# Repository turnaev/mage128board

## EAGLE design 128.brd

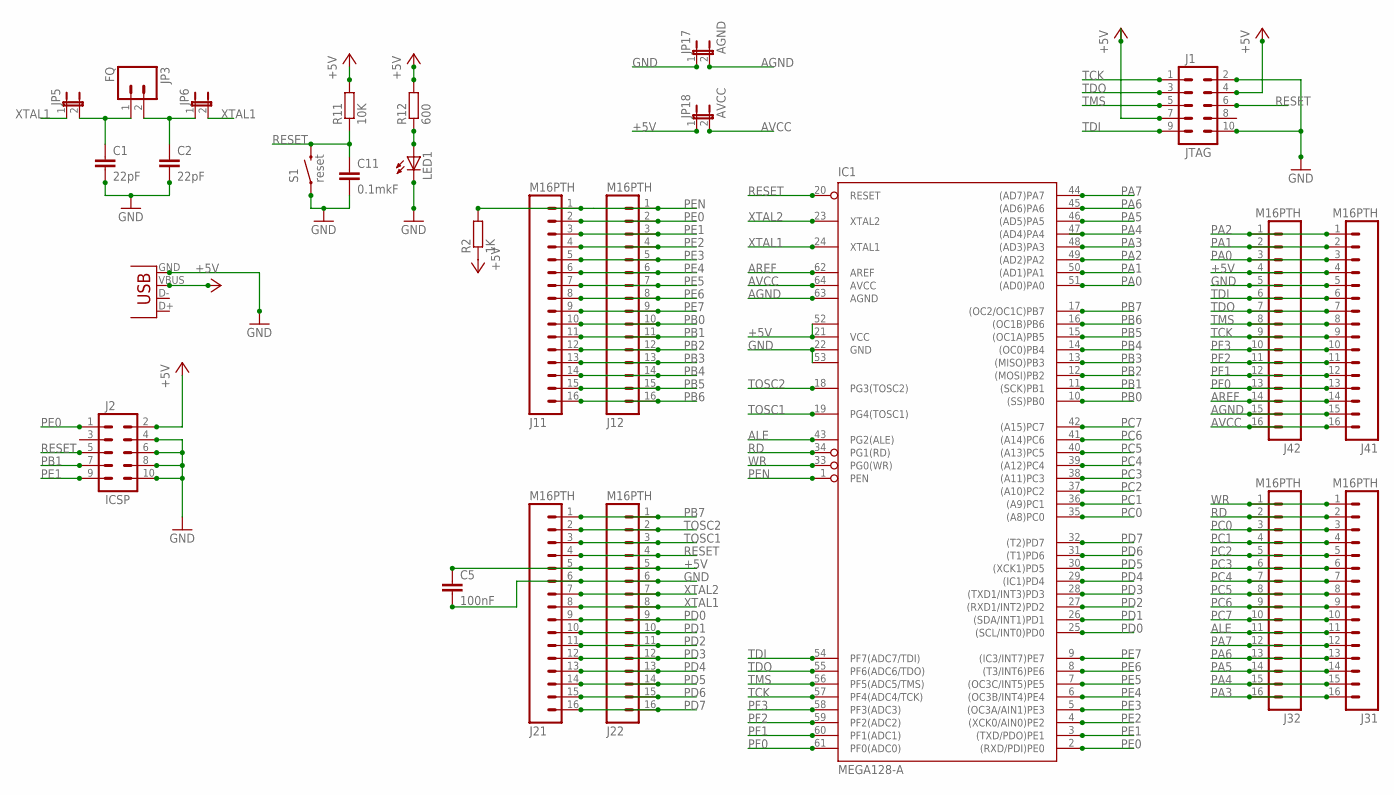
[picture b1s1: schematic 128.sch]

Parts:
C1, C2: 22pF; C0805
C5: 100nF; C0805
C11: 0.1mkF; C0805
IC1: MEGA128-A; TQFP64
J1: JTAG; 2X5-SHROUDED_LOCK
J2: ICSP; 2X5-SHROUDED_LOCK
J11, J12, J21, J22, J31, J32, J41, J42: M16PTH; 1X16
JP3: FQ; 1X02_LOCK
JP4: USBSMD; USB-MINIB
JP5, JP6: JUMPER-2PTH; 1X02
JP17: AGND; 1X02
JP18: AVCC; 1X02
LED1: LED1206; LED-1206
R2: 1K; R0805
R11: 10K; R0805
R12: 600; R0805
S1: reset; TACTILE_SWITCH_SMD-2

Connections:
+5V: C5.1, IC1.21 (VCC), IC1.52 (VCC1), J1.4, J1.7, J2.2, J21.5, J22.5, J41.4, J42.4, JP4.VBUS, JP18.1, R2.1, R11.2, R12.2
AGND: IC1.63 (AGND), J41.15, J42.15, JP17.2
ALE: IC1.43 (PG2(ALE)), J31.11, J32.11
AREF: IC1.62 (AREF), J41.14, J42.14
AVCC: IC1.64 (AVCC), J41.16, J42.16, JP18.2
GND: C1.2, C2.2, C5.2, C11.2, IC1.22 (GND), IC1.53 (GND1), J1.2, J1.10, J2.4, J2.6, J2.8, J2.10, J21.6, J22.6, J41.5, J42.5, JP4.GND, JP17.1, LED1.C, S1.2 (1)
unnamed: C1.1, JP3.1, JP5.2
unnamed: C2.1, JP3.2, JP6.1
unnamed: LED1.A, R12.1
PA0: IC1.51 ((AD0)PA0), J41.3, J42.3
PA1: IC1.50 ((AD1)PA1), J41.2, J42.2
PA2: IC1.49 ((AD2)PA2), J41.1, J42.1
PA3: IC1.48 ((AD3)PA3), J31.16, J32.16
PA4: IC1.47 ((AD4)PA4), J31.15, J32.15
PA5: IC1.46 ((AD5)PA5), J31.14, J32.14
PA6: IC1.45 ((AD6)PA6), J31.13, J32.13
PA7: IC1.44 ((AD7)PA7), J31.12, J32.12
PB0: IC1.10 ((SS)PB0), J11.10, J12.10
PB1: IC1.11 ((SCK)PB1), J2.7, J11.11, J12.11
PB2: IC1.12 ((MOSI)PB2), J11.12, J12.12
PB3: IC1.13 ((MISO)PB3), J11.13, J12.13
PB4: IC1.14 ((OC0)PB4), J11.14, J12.14
PB5: IC1.15 ((OC1A)PB5), J11.15, J12.15
PB6: IC1.16 ((OC1B)PB6), J11.16, J12.16
PB7: IC1.17 ((OC2/OC1C)PB7), J21.1, J22.1
PC0: IC1.35 ((A8)PC0), J31.3, J32.3
PC1: IC1.36 ((A9)PC1), J31.4, J32.4
PC2: IC1.37 ((A10)PC2), J31.5, J32.5
PC3: IC1.38 ((A11)PC3), J31.6, J32.6
PC4: IC1.39 ((A12)PC4), J31.7, J32.7
PC5: IC1.40 ((A13)PC5), J31.8, J32.8
PC6: IC1.41 ((A14)PC6), J31.9, J32.9
PC7: IC1.42 ((A15)PC7), J31.10, J32.10
PD0: IC1.25 ((SCL/INT0)PD0), J21.9, J22.9
PD1: IC1.26 ((SDA/INT1)PD1), J21.10, J22.10
PD2: IC1.27 ((RXD1/INT2)PD2), J21.11, J22.11
PD3: IC1.28 ((TXD1/INT3)PD3), J21.12, J22.12
PD4: IC1.29 ((IC1)PD4), J21.13, J22.13
PD5: IC1.30 ((XCK1)PD5), J21.14, J22.14
PD6: IC1.31 ((T1)PD6), J21.15, J22.15
PD7: IC1.32 ((T2)PD7), J21.16, J22.16
PE0: IC1.2 ((RXD/PDI)PE0), J2.1, J11.2, J12.2
PE1: IC1.3 ((TXD/PDO)PE1), J2.9, J11.3, J12.3
PE2: IC1.4 ((XCK0/AIN0)PE2), J11.4, J12.4
PE3: IC1.5 ((OC3A/AIN1)PE3), J11.5, J12.5
PE4: IC1.6 ((OC3B/INT4)PE4), J11.6, J12.6
PE5: IC1.7 ((OC3C/INT5)PE5), J11.7, J12.7
PE6: IC1.8 ((T3/INT6)PE6), J11.8, J12.8
PE7: IC1.9 ((IC3/INT7)PE7), J11.9, J12.9
PEN: IC1.1 (PEN), J11.1, J12.1, R2.2
PF0: IC1.61 (PF0(ADC0)), J41.13, J42.13
PF1: IC1.60 (PF1(ADC1)), J41.12, J42.12
PF2: IC1.59 (PF2(ADC2)), J41.11, J42.11
PF3: IC1.58 (PF3(ADC3)), J41.10, J42.10
RD: IC1.34 (PG1(RD)), J31.2, J32.2
RESET: C11.1, IC1.20 (RESET), J1.6, J2.5, J21.4, J22.4, R11.1, S1.1 (2)
TCK: IC1.57 (PF4(ADC4/TCK)), J1.1, J41.9, J42.9
TDI: IC1.54 (PF7(ADC7/TDI)), J1.9, J41.6, J42.6
TDO: IC1.55 (PF6(ADC6/TDO)), J1.3, J41.7, J42.7
TMS: IC1.56 (PF5(ADC5/TMS)), J1.5, J41.8, J42.8
TOSC1: IC1.19 (PG4(TOSC1)), J21.3, J22.3
TOSC2: IC1.18 (PG3(TOSC2)), J21.2, J22.2
WR: IC1.33 (PG0(WR)), J31.1, J32.1
XTAL1: IC1.24 (XTAL1), J21.8, J22.8, JP5.1, JP6.2
XTAL2: IC1.23 (XTAL2), J21.7, J22.7

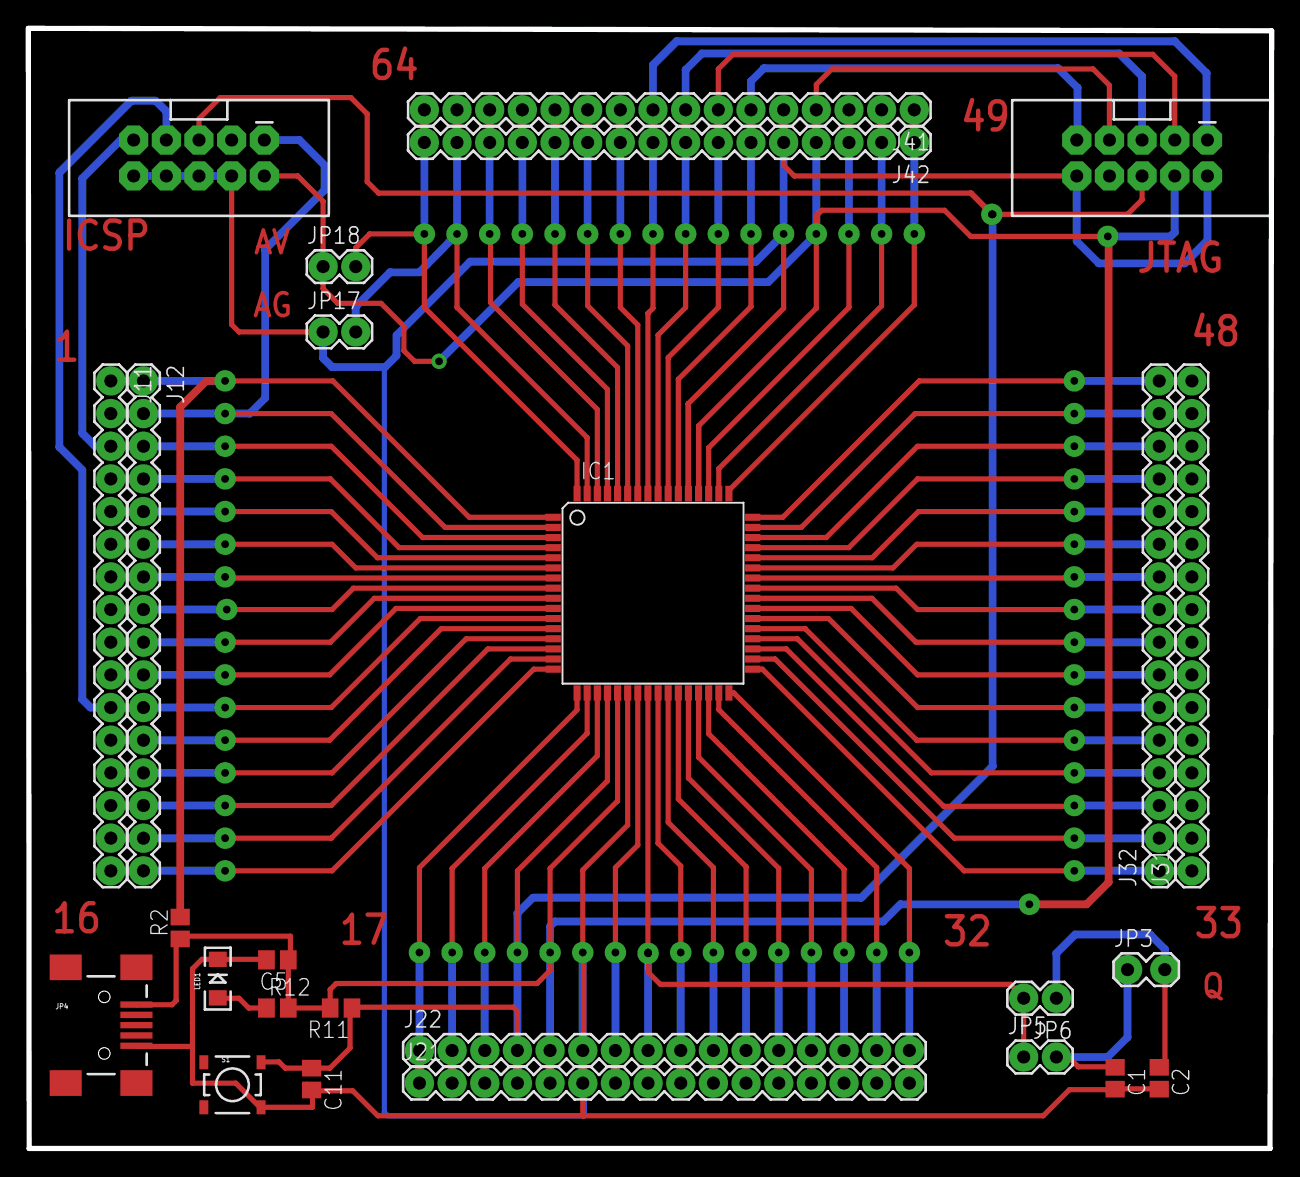
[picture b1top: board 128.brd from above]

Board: 2 copper layers, 96.7 x 87.1 mm, 26 parts (0 on the bottom side), 65 nets.

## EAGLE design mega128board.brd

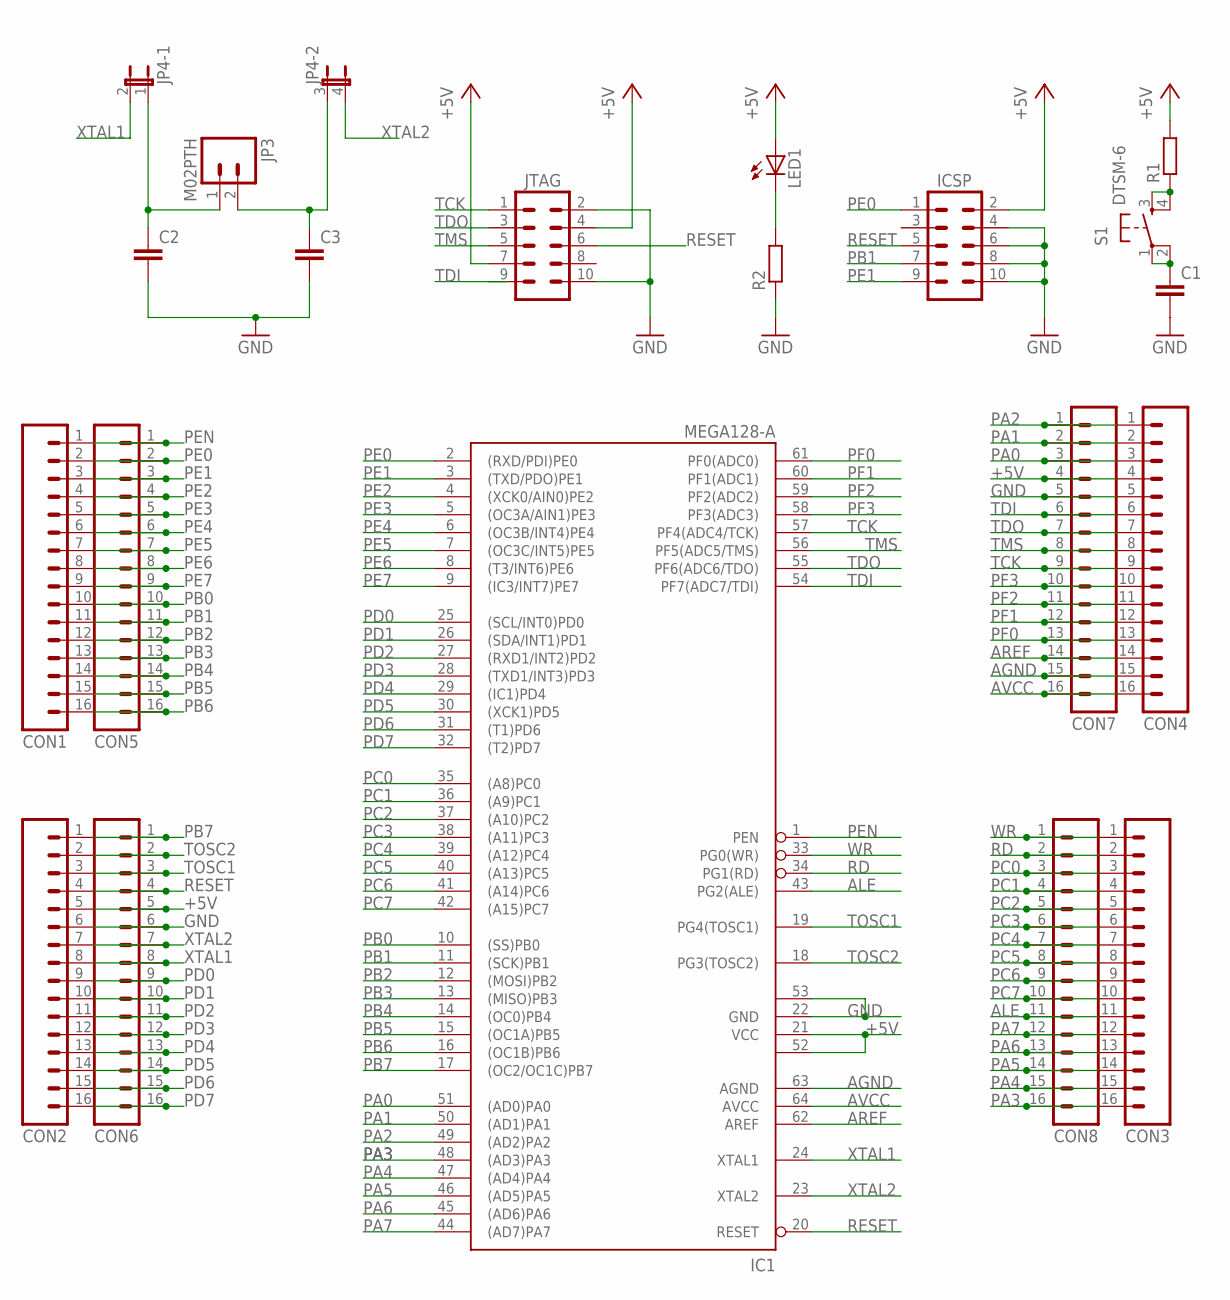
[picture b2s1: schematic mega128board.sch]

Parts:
C1, C2, C3: C-EUC0805; C0805
CON1, CON2, CON3, CON4, CON5, CON6, CON7, CON8: M161X16_NO_SILK; 1X16_NO_SILK
IC1: MEGA128-A; TQFP64
ICSP: M05X2SHD; 2X5-SHROUDED
JP3: M02PTH; 1X02
JP4: JP2QE; JP2Q
JTAG: M05X2SHD; 2X5-SHROUDED
LED1: LED1206; LED-1206
R1, R2: R-EU_M0805; M0805
S1: DTSM-6

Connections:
+5V: CON2.5, CON4.4, CON6.5, CON7.4, IC1.21 (VCC), IC1.52 (VCC1), ICSP.2, JTAG.4, JTAG.7, LED1.A, R1.2
AGND: CON4.15, CON7.15, IC1.63 (AGND)
ALE: CON3.11, CON8.11, IC1.43 (PG2(ALE))
AREF: CON4.14, CON7.14, IC1.62 (AREF)
AVCC: CON4.16, CON7.16, IC1.64 (AVCC)
GND: C1.2, C2.2, C3.2, CON2.6, CON4.5, CON6.6, CON7.5, IC1.22 (GND), IC1.53 (GND1), ICSP.4, ICSP.6, ICSP.8, ICSP.10, JTAG.2, JTAG.10, R2.1
unnamed: C1.1, S1.1, S1.2
unnamed: R1.1, S1.3, S1.4
unnamed: LED1.C, R2.2
unnamed: C3.1, JP3.2, JP4.3 (1)
unnamed: C2.1, JP3.1, JP4.1
PA0: CON4.3, CON7.3, IC1.51 ((AD0)PA0)
PA1: CON4.2, CON7.2, IC1.50 ((AD1)PA1)
PA2: CON4.1, CON7.1, IC1.49 ((AD2)PA2)
PA3: CON3.16, CON8.16, IC1.48 ((AD3)PA3)
PA4: CON3.15, CON8.15, IC1.47 ((AD4)PA4)
PA5: CON3.14, CON8.14, IC1.46 ((AD5)PA5)
PA6: CON3.13, CON8.13, IC1.45 ((AD6)PA6)
PA7: CON3.12, CON8.12, IC1.44 ((AD7)PA7)
PB0: CON1.10, CON5.10, IC1.10 ((SS)PB0)
PB1: CON1.11, CON5.11, IC1.11 ((SCK)PB1), ICSP.7
PB2: CON1.12, CON5.12, IC1.12 ((MOSI)PB2)
PB3: CON1.13, CON5.13, IC1.13 ((MISO)PB3)
PB4: CON1.14, CON5.14, IC1.14 ((OC0)PB4)
PB5: CON1.15, CON5.15, IC1.15 ((OC1A)PB5)
PB6: CON1.16, CON5.16, IC1.16 ((OC1B)PB6)
PB7: CON2.1, CON6.1, IC1.17 ((OC2/OC1C)PB7)
PC0: CON3.3, CON8.3, IC1.35 ((A8)PC0)
PC1: CON3.4, CON8.4, IC1.36 ((A9)PC1)
PC2: CON3.5, CON8.5, IC1.37 ((A10)PC2)
PC3: CON3.6, CON8.6, IC1.38 ((A11)PC3)
PC4: CON3.7, CON8.7, IC1.39 ((A12)PC4)
PC5: CON3.8, CON8.8, IC1.40 ((A13)PC5)
PC6: CON3.9, CON8.9, IC1.41 ((A14)PC6)
PC7: CON3.10, CON8.10, IC1.42 ((A15)PC7)
PD0: CON2.9, CON6.9, IC1.25 ((SCL/INT0)PD0)
PD1: CON2.10, CON6.10, IC1.26 ((SDA/INT1)PD1)
PD2: CON2.11, CON6.11, IC1.27 ((RXD1/INT2)PD2)
PD3: CON2.12, CON6.12, IC1.28 ((TXD1/INT3)PD3)
PD4: CON2.13, CON6.13, IC1.29 ((IC1)PD4)
PD5: CON2.14, CON6.14, IC1.30 ((XCK1)PD5)
PD6: CON2.15, CON6.15, IC1.31 ((T1)PD6)
PD7: CON2.16, CON6.16, IC1.32 ((T2)PD7)
PE0: CON1.2, CON5.2, IC1.2 ((RXD/PDI)PE0), ICSP.1
PE1: CON1.3, CON5.3, IC1.3 ((TXD/PDO)PE1), ICSP.9
PE2: CON1.4, CON5.4, IC1.4 ((XCK0/AIN0)PE2)
PE3: CON1.5, CON5.5, IC1.5 ((OC3A/AIN1)PE3)
PE4: CON1.6, CON5.6, IC1.6 ((OC3B/INT4)PE4)
PE5: CON1.7, CON5.7, IC1.7 ((OC3C/INT5)PE5)
PE6: CON1.8, CON5.8, IC1.8 ((T3/INT6)PE6)
PE7: CON1.9, CON5.9, IC1.9 ((IC3/INT7)PE7)
PEN: CON1.1, CON5.1, IC1.1 (PEN)
PF0: CON4.13, CON7.13, IC1.61 (PF0(ADC0))
PF1: CON4.12, CON7.12, IC1.60 (PF1(ADC1))
PF2: CON4.11, CON7.11, IC1.59 (PF2(ADC2))
PF3: CON4.10, CON7.10, IC1.58 (PF3(ADC3))
RD: CON3.2, CON8.2, IC1.34 (PG1(RD))
RESET: CON2.4, CON6.4, IC1.20 (RESET), ICSP.5, JTAG.6
TCK: CON4.9, CON7.9, IC1.57 (PF4(ADC4/TCK)), JTAG.1
TDI: CON4.6, CON7.6, IC1.54 (PF7(ADC7/TDI))
TDO: CON4.7, CON7.7, IC1.55 (PF6(ADC6/TDO)), JTAG.3
TMS: CON4.8, CON7.8, IC1.56 (PF5(ADC5/TMS)), JTAG.5
TOSC1: CON2.3, CON6.3, IC1.19 (PG4(TOSC1))
TOSC2: CON2.2, CON6.2, IC1.18 (PG3(TOSC2))
WR: CON3.1, CON8.1, IC1.33 (PG0(WR))
XTAL1: CON2.8, CON6.8, IC1.24 (XTAL1), JP4.2
XTAL2: CON2.7, CON6.7, IC1.23 (XTAL2), JP4.4 (2)

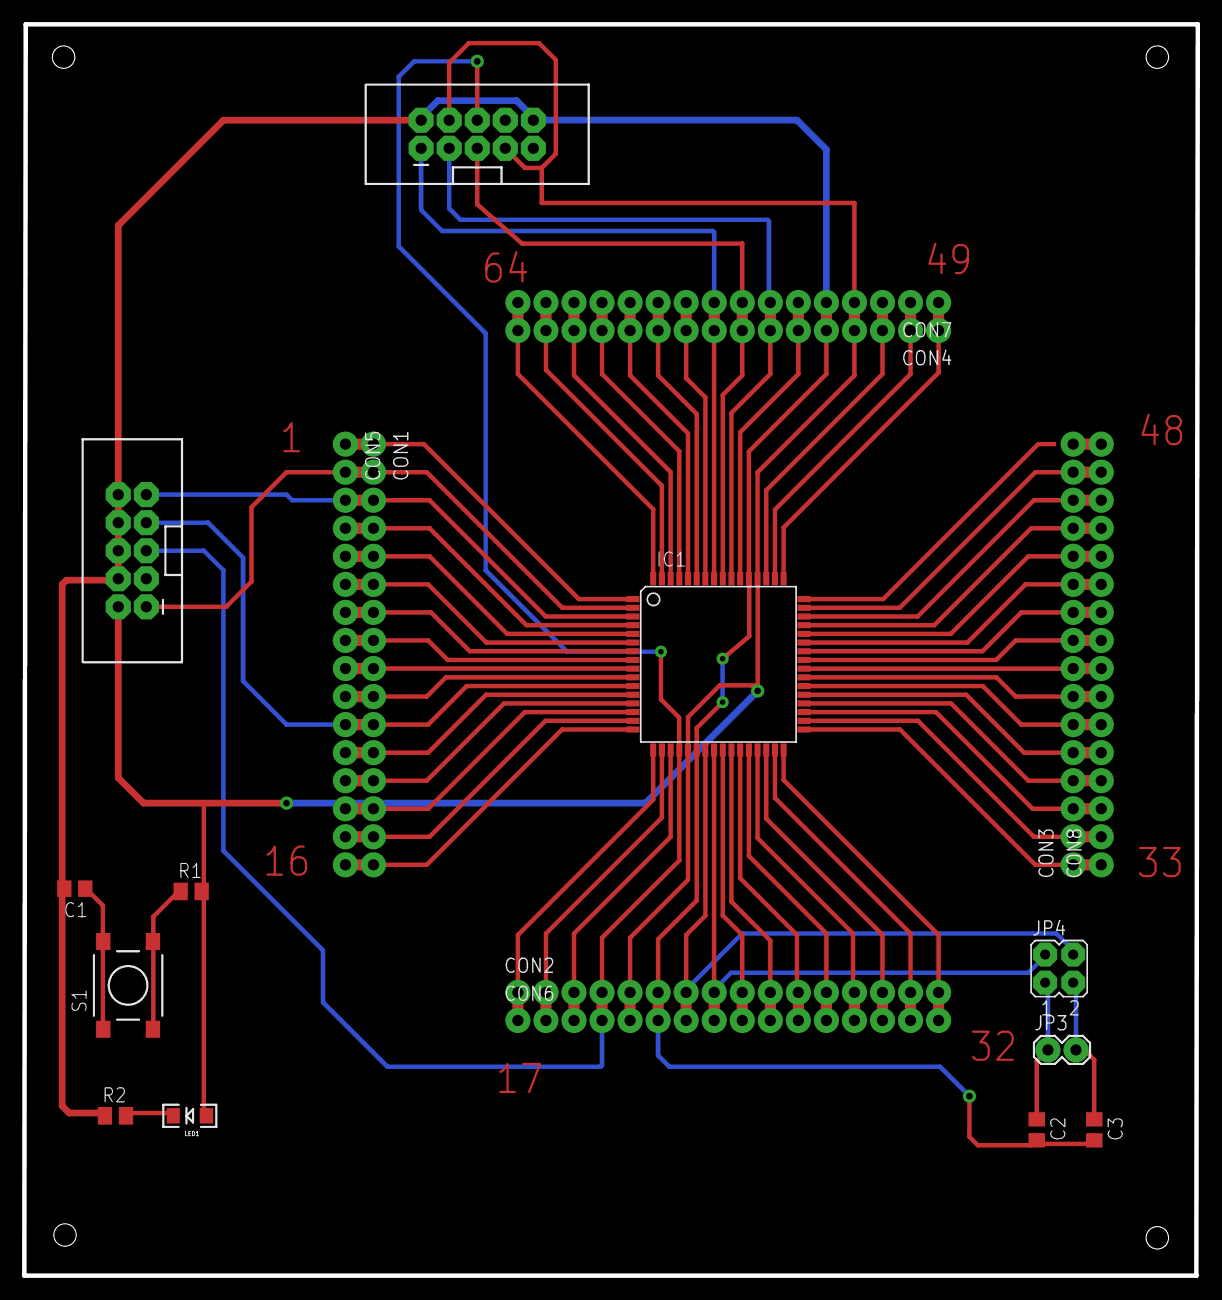
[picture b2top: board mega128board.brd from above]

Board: 2 copper layers, 106.3 x 113.3 mm, 20 parts (0 on the bottom side), 67 nets.

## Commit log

2014-03-31 init

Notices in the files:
parts and their libraries:
SparkFun-Connectors: Licensing: Creative Commons ShareAlike 4.0 International - https://creativecommons.org/licenses/by-sa/4.0
